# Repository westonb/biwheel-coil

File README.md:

# biwheel-coil
A portable (bike mounted) QCW Tesla Coil.

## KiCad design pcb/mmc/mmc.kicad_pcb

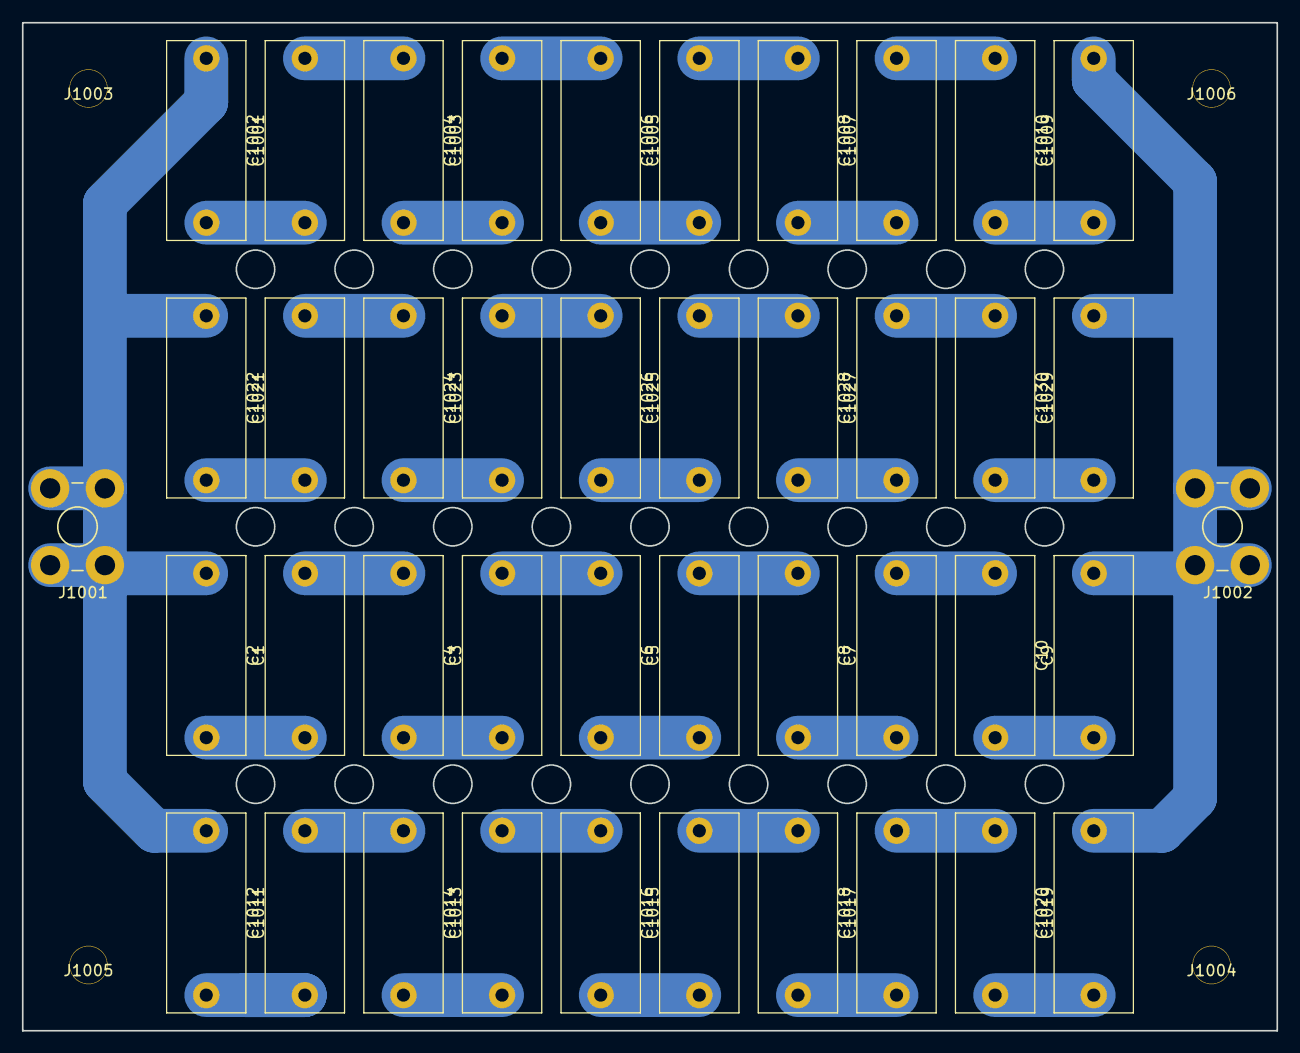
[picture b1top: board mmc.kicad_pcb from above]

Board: 2 copper layers, 114.5 x 92.0 mm, 46 parts (0 on the bottom side), 38 nets.

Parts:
C1, C2, C3, C4, C5, C6, C7, C8, C9, C10, C1001, C1002, C1003, C1004, C1005, C1006, C1007, C1008, C1009, C1010, C1011, C1012, C1013, C1014, C1015, C1016, C1017, C1018, C1019, C1020, C1021, C1022, C1023, C1024, C1025, C1026, C1027, C1028, C1029, C1030: 33n; C_Rect_L18.0mm_W7.0mm_P15.00mm_FKS3_FKP3
J1001, J1002: Conn_01x01_Female; 7693-term
J1003, J1004, J1005, J1006: mounting-hole-nc; M3-mounting-hole-insulated

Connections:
unnamed: C1.1, C1001.1, C1011.1, C1021.1, J1001.1
unnamed: C1.2, C2.1
unnamed: C2.2, C3.1
unnamed: C3.2, C4.1
unnamed: C4.2, C5.1
unnamed: C5.2, C6.1
unnamed: C6.2, C7.1
unnamed: C7.2, C8.1
unnamed: C8.2, C9.1
unnamed: C9.2, C10.1
unnamed: C10.2, C1010.2, C1020.2, C1030.2, J1002.1
unnamed: C1001.2, C1002.1
unnamed: C1002.2, C1003.1
unnamed: C1003.2, C1004.1
unnamed: C1004.2, C1005.1
unnamed: C1005.2, C1006.1
unnamed: C1006.2, C1007.1
unnamed: C1007.2, C1008.1
unnamed: C1008.2, C1009.1
unnamed: C1009.2, C1010.1
unnamed: C1011.2, C1012.1
unnamed: C1012.2, C1013.1
unnamed: C1013.2, C1014.1
unnamed: C1014.2, C1015.1
unnamed: C1015.2, C1016.1
unnamed: C1016.2, C1017.1
unnamed: C1017.2, C1018.1
unnamed: C1018.2, C1019.1
unnamed: C1019.2, C1020.1
unnamed: C1021.2, C1022.1
unnamed: C1022.2, C1023.1
unnamed: C1023.2, C1024.1
unnamed: C1024.2, C1025.1
unnamed: C1025.2, C1026.1
unnamed: C1026.2, C1027.1
unnamed: C1027.2, C1028.1
unnamed: C1028.2, C1029.1
unnamed: C1029.2, C1030.1

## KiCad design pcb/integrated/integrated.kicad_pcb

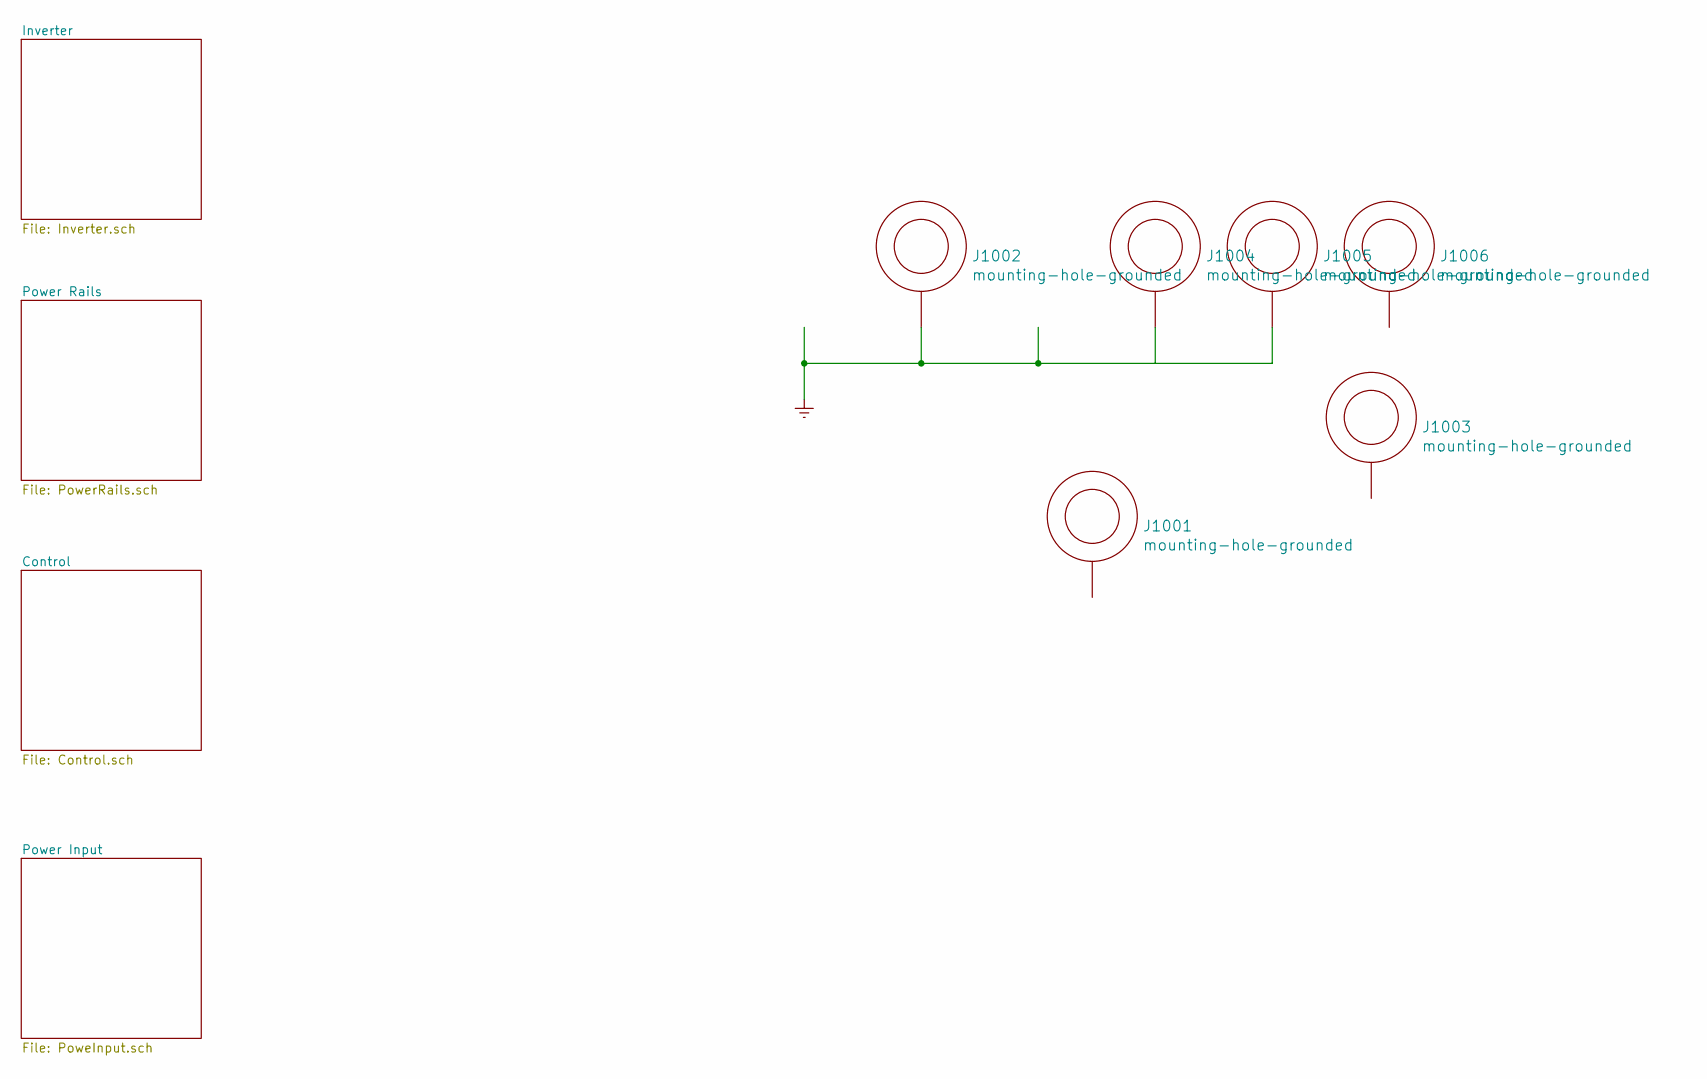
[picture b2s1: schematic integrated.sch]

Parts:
J1001, J1002, J1003, J1004, J1005, J1006: mounting-hole-grounded; M3-tight-fit-pan-head

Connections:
Earth: J1002.1, J1004.1, J1005.1; also elsewhere on the board

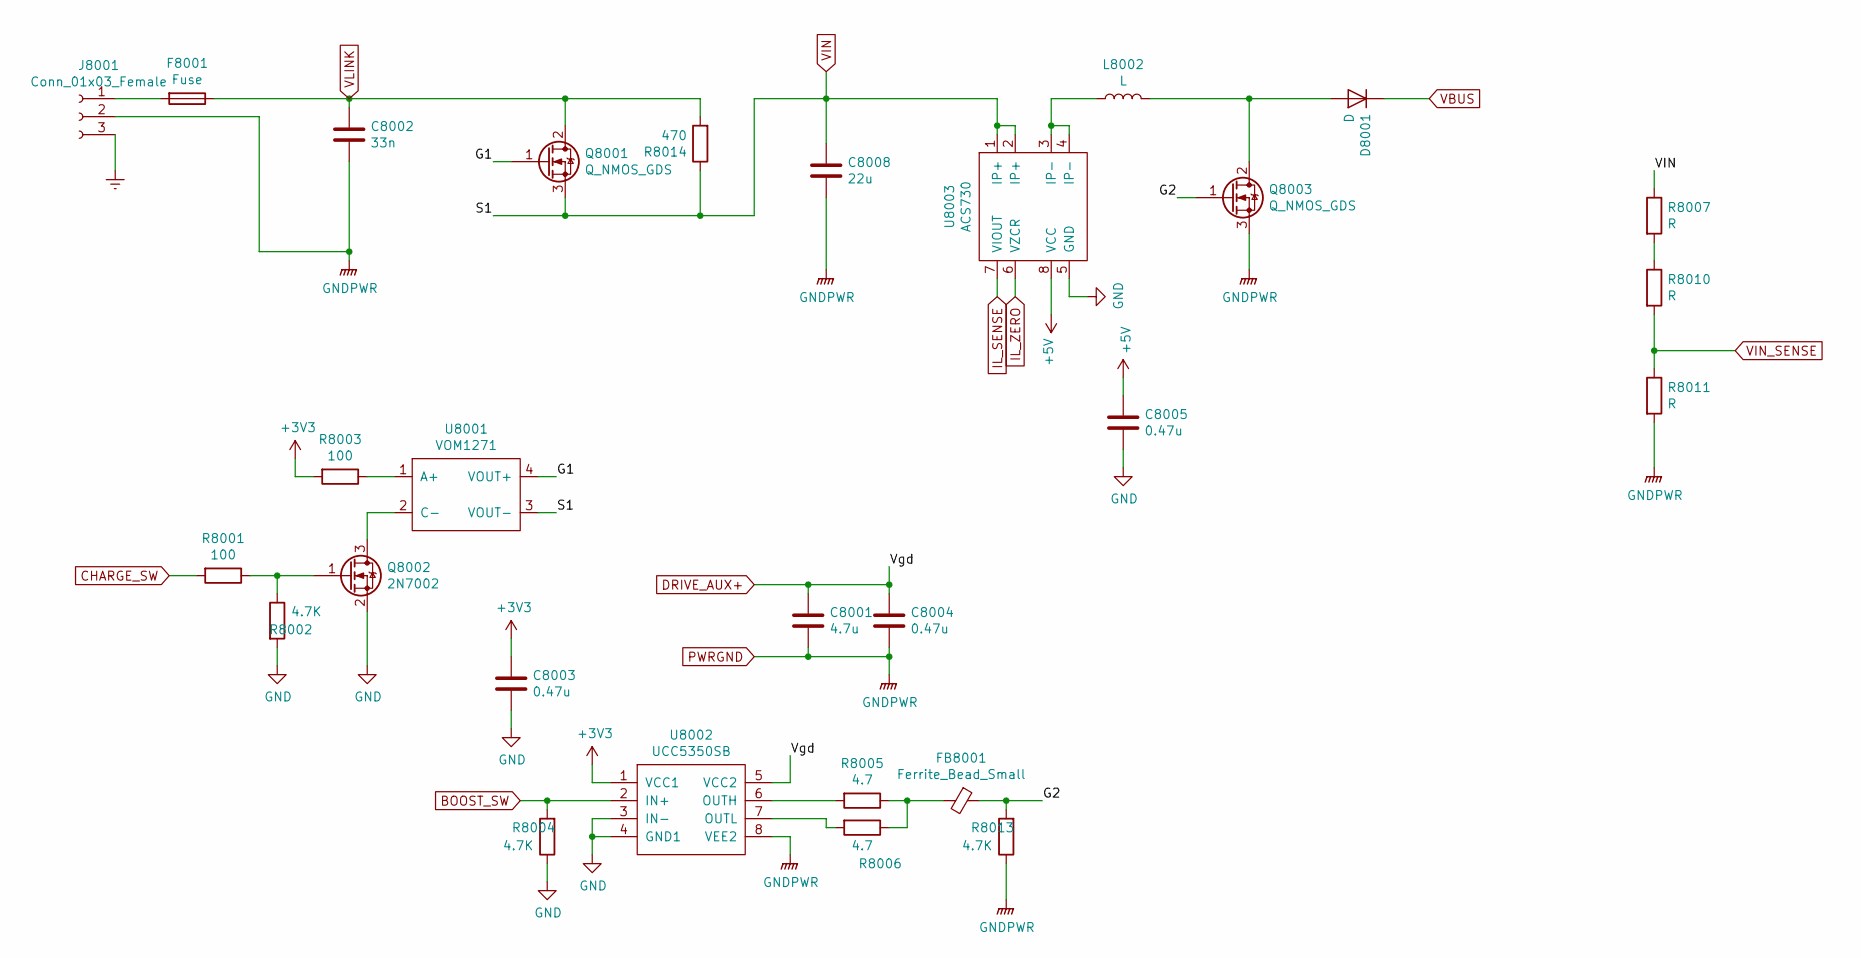
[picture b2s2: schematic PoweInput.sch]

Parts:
C8001: 4.7u; C_0805_2012Metric
C8002: 33n; C_Rect_L18.0mm_W7.0mm_P15.00mm_FKS3_FKP3
C8003, C8004, C8005: 0.47u; C_0603_1608Metric
C8008: 22u; C_Rect_L33.0mm_W13.0mm_P27.50mm_MKS4
D8001: D; TO-247_2_horizontal_under
F8001: Fuse; Fuseholder_Cylinder-5x20mm_Schurter_0031_8201_Horizontal_Op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
FB8001: Ferrite_Bead_Small; L_0805_2012Metric
J8001: Conn_01x03_Female; Terminal-block-plug_3x1_5mm-pitch
L8002: L; T157-Vertical
Q8001, Q8003: Q_NMOS_GDS; TO-247_3_horizontal_under
Q8002: 2N7002; SOT-23
R8001, R8003: 100; R_0402_1005Metric
R8002: 4.7K; R_0402_1005Metric
R8004, R8013: 4.7K; R_0603_1608Metric
R8005, R8006: 4.7; R_0805_2012Metric
R8007, R8010, R8011: R; R_0805_2012Metric
R8014: 470; TO-247_2_horizontal_under
U8001: VOM1271; SO-4_4.4x4.3mm_P2.54mm
U8002: UCC5350SB; SOIC-8_3.9x4.9mm_P1.27mm
U8003: ACS730; SOIC-8_3.9x4.9mm_P1.27mm

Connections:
+3V3: C8003.1, R8003.2, U8002.1 (VCC1); also elsewhere on the board
+5V: C8005.1, U8003.8 (VCC); also elsewhere on the board
/Power Input/G1: Q8001.1 (G), U8001.4 (VOUT+)
/Power Input/G2: FB8001.1, Q8003.1 (G), R8013.2
BOOST_SW: R8004.2, U8002.2 (IN+); also elsewhere on the board
CHARGE_SW: R8001.2; also elsewhere on the board
DRIVE_AUX+: C8001.1, C8004.1, U8002.5 (VCC2); also elsewhere on the board
Earth: J8001.3; also elsewhere on the board
GND: C8003.2, C8005.2, Q8002.2 (S), R8002.2, R8004.1, U8002.3 (IN-), U8002.4 (GND1), U8003.5 (GND); also elsewhere on the board
IL_SENSE: U8003.7 (VIOUT); also elsewhere on the board
IL_ZERO: U8003.6 (VZCR)
unnamed: D8001.2 (A), L8002.2, Q8003.2 (D)
unnamed: F8001.2, J8001.1
unnamed: FB8001.2, R8005.1, R8006.1
unnamed: L8002.1, U8003.3 (IP-), U8003.4 (IP-)
unnamed: Q8002.1 (G), R8001.1, R8002.1
unnamed: Q8002.3 (D), U8001.2 (C-)
unnamed: R8003.1, U8001.1 (A+)
unnamed: R8005.2, U8002.6 (OUTH)
unnamed: R8006.2, U8002.7 (OUTL)
unnamed: R8007.2, R8010.1
PWRGND: C8001.2, C8002.2, C8004.2, C8008.2, J8001.2, Q8003.3 (S), R8011.2, R8013.1, U8002.8 (VEE2); also elsewhere on the board
VBUS: D8001.1 (K); also elsewhere on the board
VIN: C8008.1, Q8001.3 (S), R8007.1, R8014.1, U8001.3 (VOUT-), U8003.1 (IP+), U8003.2 (IP+)
VIN_SENSE: R8010.2, R8011.1; also elsewhere on the board
VLINK: C8002.1, F8001.1, Q8001.2 (D), R8014.2; also elsewhere on the board

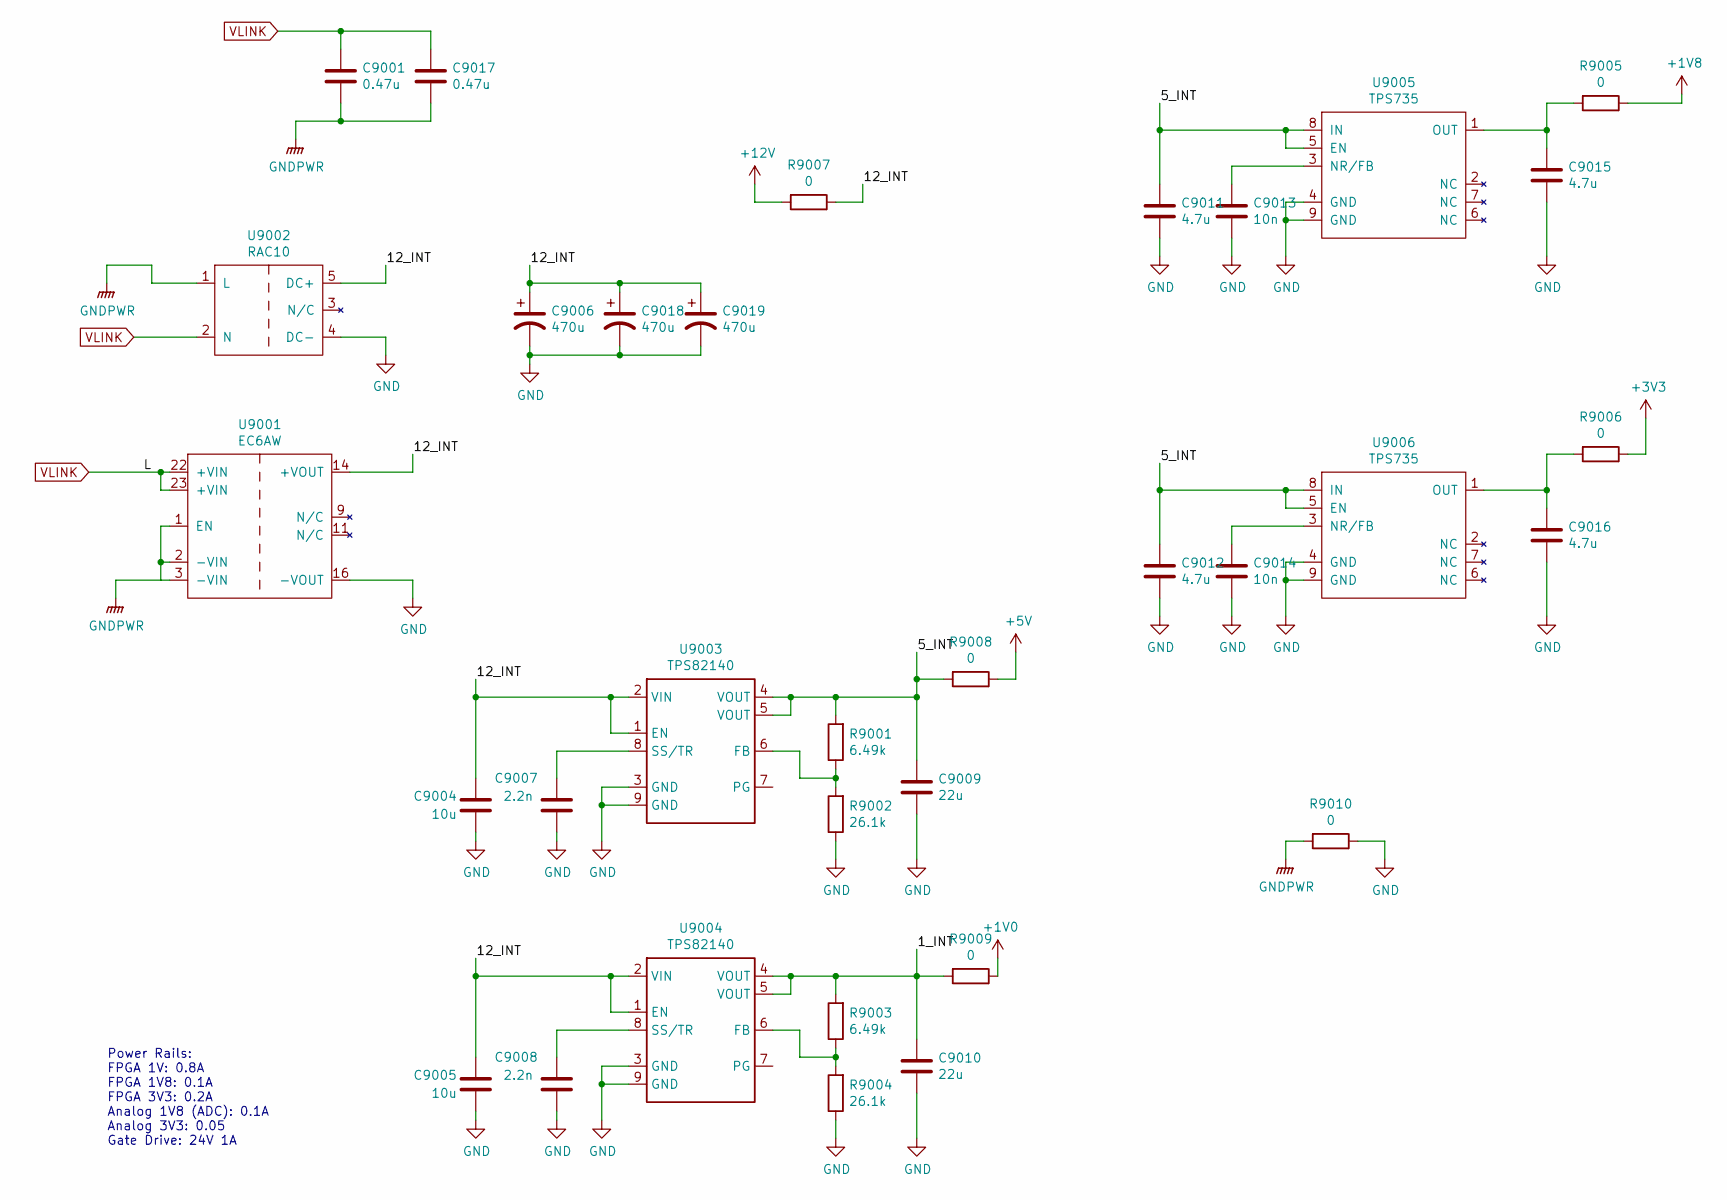
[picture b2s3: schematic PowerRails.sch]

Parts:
C9001, C9017: 0.47u; C_1812_4532Metric
C9004, C9005: 10u; C_1206_3216Metric
C9006, C9018, C9019: 470u; CP_Radial_D10.0mm_P5.00mm
C9007, C9008: 2.2n; C_0402_1005Metric
C9009, C9010: 22u; C_0805_2012Metric
C9011, C9012, C9015, C9016: 4.7u; C_0603_1608Metric
C9013, C9014: 10n; C_0402_1005Metric
R9001, R9003: 6.49k; R_0402_1005Metric
R9002, R9004: 26.1k; R_0402_1005Metric
R9005, R9006, R9007, R9008, R9009, R9010: 0; R_0805_2012Metric
U9001: EC6AW
U9002: RAC10
U9003, U9004: TPS82140; uSil-8
U9005, U9006: TPS735; SON-8_EP

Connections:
+1V0: R9009.1; also elsewhere on the board
+1V8: R9005.1; also elsewhere on the board
+3V3: R9006.1; also elsewhere on the board
+5V: R9008.1; also elsewhere on the board
+12V: R9007.2; also elsewhere on the board
/Power Rails/1_INT: C9010.1, R9003.2, R9009.2, U9004.4 (VOUT), U9004.5 (VOUT)
/Power Rails/5_INT: C9009.1, C9011.2, C9012.2, R9001.2, R9008.2, U9003.4 (VOUT), U9003.5 (VOUT), U9005.5 (EN), U9005.8 (IN), U9006.5 (EN), U9006.8 (IN)
/Power Rails/12_INT: C9004.1, C9005.1, C9006.1, C9018.1, C9019.1, R9007.1, U9001.14 (+VOUT), U9002.5 (DC+), U9003.1 (EN), U9003.2 (VIN), U9004.1 (EN), U9004.2 (VIN)
GND: C9004.2, C9005.2, C9006.2, C9007.2, C9008.2, C9009.2, C9010.2, C9011.1, C9012.1, C9013.1, C9014.1, C9015.1, C9016.1, C9018.2, C9019.2, R9002.1, R9004.1, R9010.1, U9001.16 (-VOUT), U9002.4 (DC-), U9003.3 (GND), U9003.9 (GND), U9004.3 (GND), U9004.9 (GND), U9005.4 (GND), U9005.9 (GND), U9006.4 (GND), U9006.9 (GND); also elsewhere on the board
unnamed: C9007.1, U9003.8 (SS/TR)
unnamed: C9008.1, U9004.8 (SS/TR)
unnamed: C9013.2, U9005.3 (NR/FB)
unnamed: C9014.2, U9006.3 (NR/FB)
unnamed: C9015.2, R9005.2, U9005.1 (OUT)
unnamed: C9016.2, R9006.2, U9006.1 (OUT)
unnamed: R9001.1, R9002.2, U9003.6 (FB)
unnamed: R9003.1, R9004.2, U9004.6 (FB)
PWRGND: C9001.2, C9017.2, R9010.2, U9001.1 (EN), U9001.2 (-VIN), U9001.3 (-VIN), U9002.1 (L); also elsewhere on the board
VLINK: C9001.1, C9017.1, U9001.22 (+VIN), U9001.23 (+VIN), U9002.2 (N); also elsewhere on the board

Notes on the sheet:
Power Rails: FPGA 1V: 0.8A FPGA 1V8: 0.1A FPGA 3V3: 0.2A Analog 1V8 (ADC): 0.1A Analog 3V3: 0.05 Gate Drive: 24V 1A

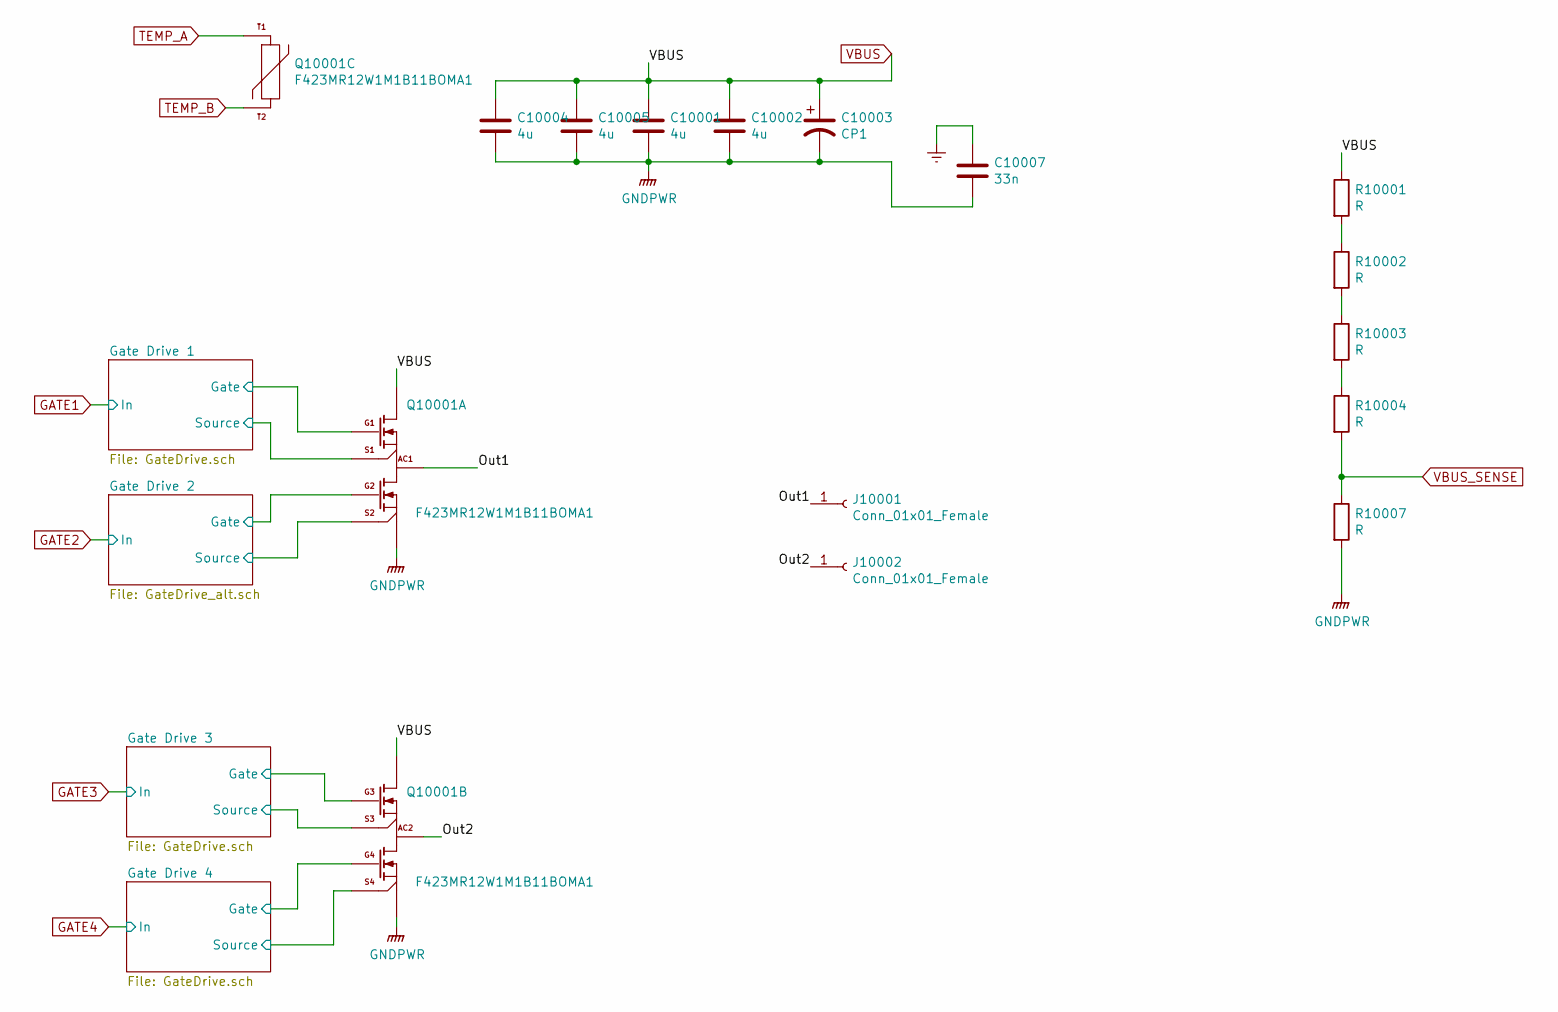
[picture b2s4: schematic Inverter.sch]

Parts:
C10001, C10002, C10004, C10005: 4u; C_Rect_L31.5mm_W13.0mm_P27.50mm_MKS4
C10003: CP1; CAP_77mm_stud_horizontal
C10007: 33n; C_Rect_L18.0mm_W7.0mm_P15.00mm_FKS3_FKP3
J10001, J10002: Conn_01x01_Female; 7693-term
Q10001: F423MR12W1M1B11BOMA1
R10001, R10002, R10003, R10004, R10007: R; R_0805_2012Metric

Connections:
/Inverter/Gate Drive 1/Gate: Q10001.G1; also elsewhere on the board
/Inverter/Gate Drive 2/Gate: Q10001.G2; also elsewhere on the board
/Inverter/Gate Drive 3/Gate: Q10001.G3; also elsewhere on the board
/Inverter/Gate Drive 3/Source: Q10001.S3; also elsewhere on the board
/Inverter/Gate Drive 4/Gate: Q10001.G4; also elsewhere on the board
/Inverter/Gate Drive 4/Source: Q10001.S4; also elsewhere on the board
/Inverter/Out1: J10001.1, Q10001.AC1
/Inverter/Out2: J10002.1, Q10001.AC2
Earth: C10007.1; also elsewhere on the board
unnamed: R10001.2, R10002.1
unnamed: R10002.2, R10003.1
unnamed: R10003.2, R10004.1
PWRGND: C10001.2, C10002.2, C10003.2, C10004.2, C10005.2, C10007.2, Q10001.DC-, R10007.2; also elsewhere on the board
TEMP_A: Q10001.T1; also elsewhere on the board
TEMP_B: Q10001.T2; also elsewhere on the board
VBUS: C10001.1, C10002.1, C10003.1, C10004.1, C10005.1, Q10001.DC+, R10001.1; also elsewhere on the board
VBUS_SENSE: R10004.2, R10007.1; also elsewhere on the board

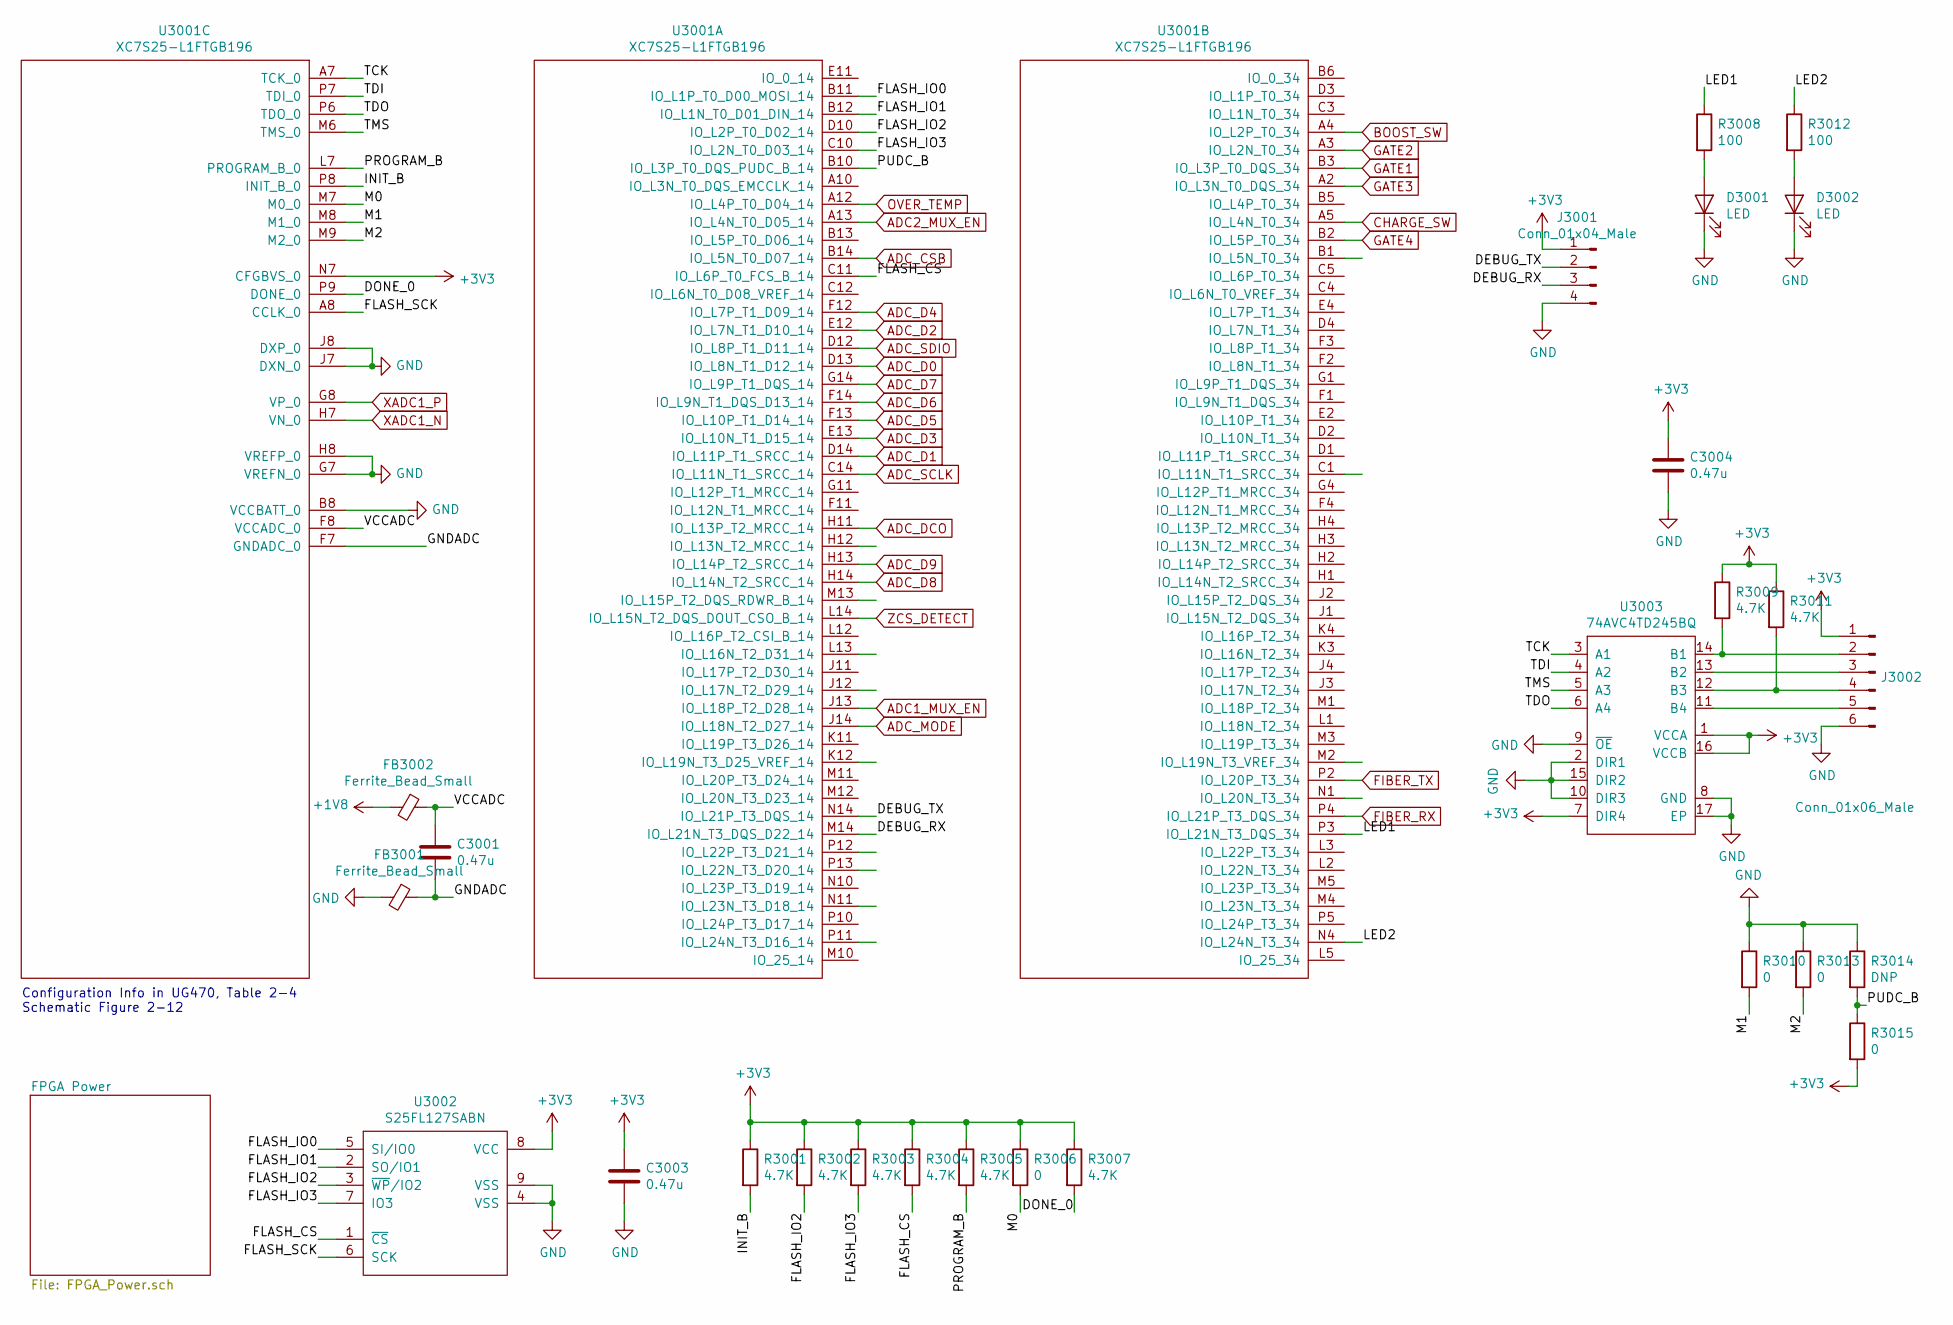
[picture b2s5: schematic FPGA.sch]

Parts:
C3001, C3003, C3004: 0.47u; C_0402_1005Metric
D3001, D3002: LED; LED_0805_2012Metric
FB3001, FB3002: Ferrite_Bead_Small; L_0402_1005Metric
J3001: Conn_01x04_Male; PinHeader_1x04_P2.54mm_Vertical
J3002: Conn_01x06_Male; PinHeader_1x06_P2.54mm_Vertical
R3001, R3002, R3003, R3004, R3005, R3007, R3009, R3011: 4.7K; R_0402_1005Metric
R3006, R3010, R3013, R3015: 0; R_0402_1005Metric
R3008, R3012: 100; R_0402_1005Metric
R3014: DNP; R_0402_1005Metric
U3001: XC7S25-L1FTGB196; FTGB196
U3002: S25FL127SABN; WSON-8-1EP_6x5mm_P1.27mm_EP3.4x4mm
U3003: 74AVC4TD245BQ; DHVQFN16

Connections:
+1V8: FB3002.2; also elsewhere on the board
+3V3: C3003.1, C3004.1, J3001.1, J3002.1, R3001.1, R3002.1, R3003.1, R3004.1, R3005.1, R3006.1, R3007.1, R3009.1, R3011.1, R3015.2, U3001.N7 (CFGBVS_0), U3002.8 (VCC), U3003.1 (VCCA), U3003.7 (DIR4), U3003.16 (VCCB); also elsewhere on the board
/Control/FPGA/DEBUG_RX: J3001.3, U3001.M14 (IO_L21N_T3_DQS_D22_14)
/Control/FPGA/DEBUG_TX: J3001.2, U3001.N14 (IO_L21P_T3_DQS_14)
/Control/FPGA/DONE_0: R3007.2, U3001.P9 (DONE_0)
/Control/FPGA/FLASH_CS: R3004.2, U3001.C11 (IO_L6P_T0_FCS_B_14), U3002.1 (~CS)
/Control/FPGA/FLASH_IO0: U3001.B11 (IO_L1P_T0_D00_MOSI_14), U3002.5 (SI/IO0)
/Control/FPGA/FLASH_IO1: U3001.B12 (IO_L1N_T0_D01_DIN_14), U3002.2 (SO/IO1)
/Control/FPGA/FLASH_IO2: R3002.2, U3001.D10 (IO_L2P_T0_D02_14), U3002.3 (~WP~/IO2)
/Control/FPGA/FLASH_IO3: R3003.2, U3001.C10 (IO_L2N_T0_D03_14), U3002.7 (IO3)
/Control/FPGA/FLASH_SCK: U3001.A8 (CCLK_0), U3002.6 (SCK)
/Control/FPGA/GNDADC: C3001.2, FB3001.1, U3001.F7 (GNDADC_0)
/Control/FPGA/INIT_B: R3001.2, U3001.P8 (INIT_B_0)
/Control/FPGA/LED1: R3008.1, U3001.P3 (IO_L21N_T3_DQS_34)
/Control/FPGA/LED2: R3012.1, U3001.N4 (IO_L24N_T3_34)
/Control/FPGA/M0: R3006.2, U3001.M7 (M0_0)
/Control/FPGA/M1: R3010.2, U3001.M8 (M1_0)
/Control/FPGA/M2: R3013.2, U3001.M9 (M2_0)
/Control/FPGA/PROGRAM_B: R3005.2, U3001.L7 (PROGRAM_B_0)
/Control/FPGA/PUDC_B: R3014.2, R3015.1, U3001.B10 (IO_L3P_T0_DQS_PUDC_B_14)
/Control/FPGA/TCK: U3001.A7 (TCK_0), U3003.3 (A1)
/Control/FPGA/TDI: U3001.P7 (TDI_0), U3003.4 (A2)
/Control/FPGA/TDO: U3001.P6 (TDO_0), U3003.6 (A4)
/Control/FPGA/TMS: U3001.M6 (TMS_0), U3003.5 (A3)
/Control/FPGA/VCCADC: C3001.1, FB3002.1, U3001.F8 (VCCADC_0)
ADC1_MUX_EN: U3001.J13 (IO_L18P_T2_D28_14); also elsewhere on the board
ADC2_MUX_EN: U3001.A13 (IO_L4N_T0_D05_14); also elsewhere on the board
ADC_CSB: U3001.B14 (IO_L5N_T0_D07_14); also elsewhere on the board
ADC_D0: U3001.D13 (IO_L8N_T1_D12_14); also elsewhere on the board
ADC_D1: U3001.D14 (IO_L11P_T1_SRCC_14); also elsewhere on the board
ADC_D2: U3001.E12 (IO_L7N_T1_D10_14); also elsewhere on the board
ADC_D3: U3001.E13 (IO_L10N_T1_D15_14); also elsewhere on the board
ADC_D4: U3001.F12 (IO_L7P_T1_D09_14); also elsewhere on the board
ADC_D5: U3001.F13 (IO_L10P_T1_D14_14); also elsewhere on the board
ADC_D6: U3001.F14 (IO_L9N_T1_DQS_D13_14); also elsewhere on the board
ADC_D7: U3001.G14 (IO_L9P_T1_DQS_14); also elsewhere on the board
ADC_D8: U3001.H14 (IO_L14N_T2_SRCC_14); also elsewhere on the board
ADC_D9: U3001.H13 (IO_L14P_T2_SRCC_14); also elsewhere on the board
ADC_DCO: U3001.H11 (IO_L13P_T2_MRCC_14); also elsewhere on the board
ADC_MODE: U3001.J14 (IO_L18N_T2_D27_14); also elsewhere on the board
ADC_SCLK: U3001.C14 (IO_L11N_T1_SRCC_14); also elsewhere on the board
ADC_SDIO: U3001.D12 (IO_L8P_T1_D11_14); also elsewhere on the board
BOOST_SW: U3001.A4 (IO_L2P_T0_34); also elsewhere on the board
CHARGE_SW: U3001.A5 (IO_L4N_T0_34); also elsewhere on the board
FIBER_RX: U3001.P4 (IO_L21P_T3_DQS_34); also elsewhere on the board
FIBER_TX: U3001.P2 (IO_L20P_T3_34); also elsewhere on the board
GATE1: U3001.B3 (IO_L3P_T0_DQS_34); also elsewhere on the board
GATE2: U3001.A3 (IO_L2N_T0_34); also elsewhere on the board
GATE3: U3001.A2 (IO_L3N_T0_DQS_34); also elsewhere on the board
GATE4: U3001.B2 (IO_L5P_T0_34); also elsewhere on the board
GND: C3003.2, C3004.2, D3001.1 (K), D3002.1 (K), FB3001.2, J3001.4, J3002.6, R3010.1, R3013.1, R3014.1, U3001.B8 (VCCBATT_0), U3001.G7 (VREFN_0), U3001.H8 (VREFP_0), U3001.J7 (DXN_0), U3001.J8 (DXP_0), U3002.4 (VSS), U3002.9 (VSS), U3003.2 (DIR1), U3003.8 (GND), U3003.9 (~OE), U3003.10 (DIR3), U3003.15 (DIR2), U3003.17 (EP); also elsewhere on the board
unnamed: D3001.2 (A), R3008.2
unnamed: D3002.2 (A), R3012.2
unnamed: J3002.2, R3009.2, U3003.14 (B1)
unnamed: J3002.3, U3003.13 (B2)
unnamed: J3002.4, R3011.2, U3003.12 (B3)
unnamed: J3002.5, U3003.11 (B4)
OVER_TEMP: U3001.A12 (IO_L4P_T0_D04_14); also elsewhere on the board
XADC1_N: U3001.H7 (VN_0); also elsewhere on the board
XADC1_P: U3001.G8 (VP_0); also elsewhere on the board
ZCS_DETECT: U3001.L14 (IO_L15N_T2_DQS_DOUT_CSO_B_14); also elsewhere on the board

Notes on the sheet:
Configuration Info in UG470, Table 2-4 Schematic Figure 2-12

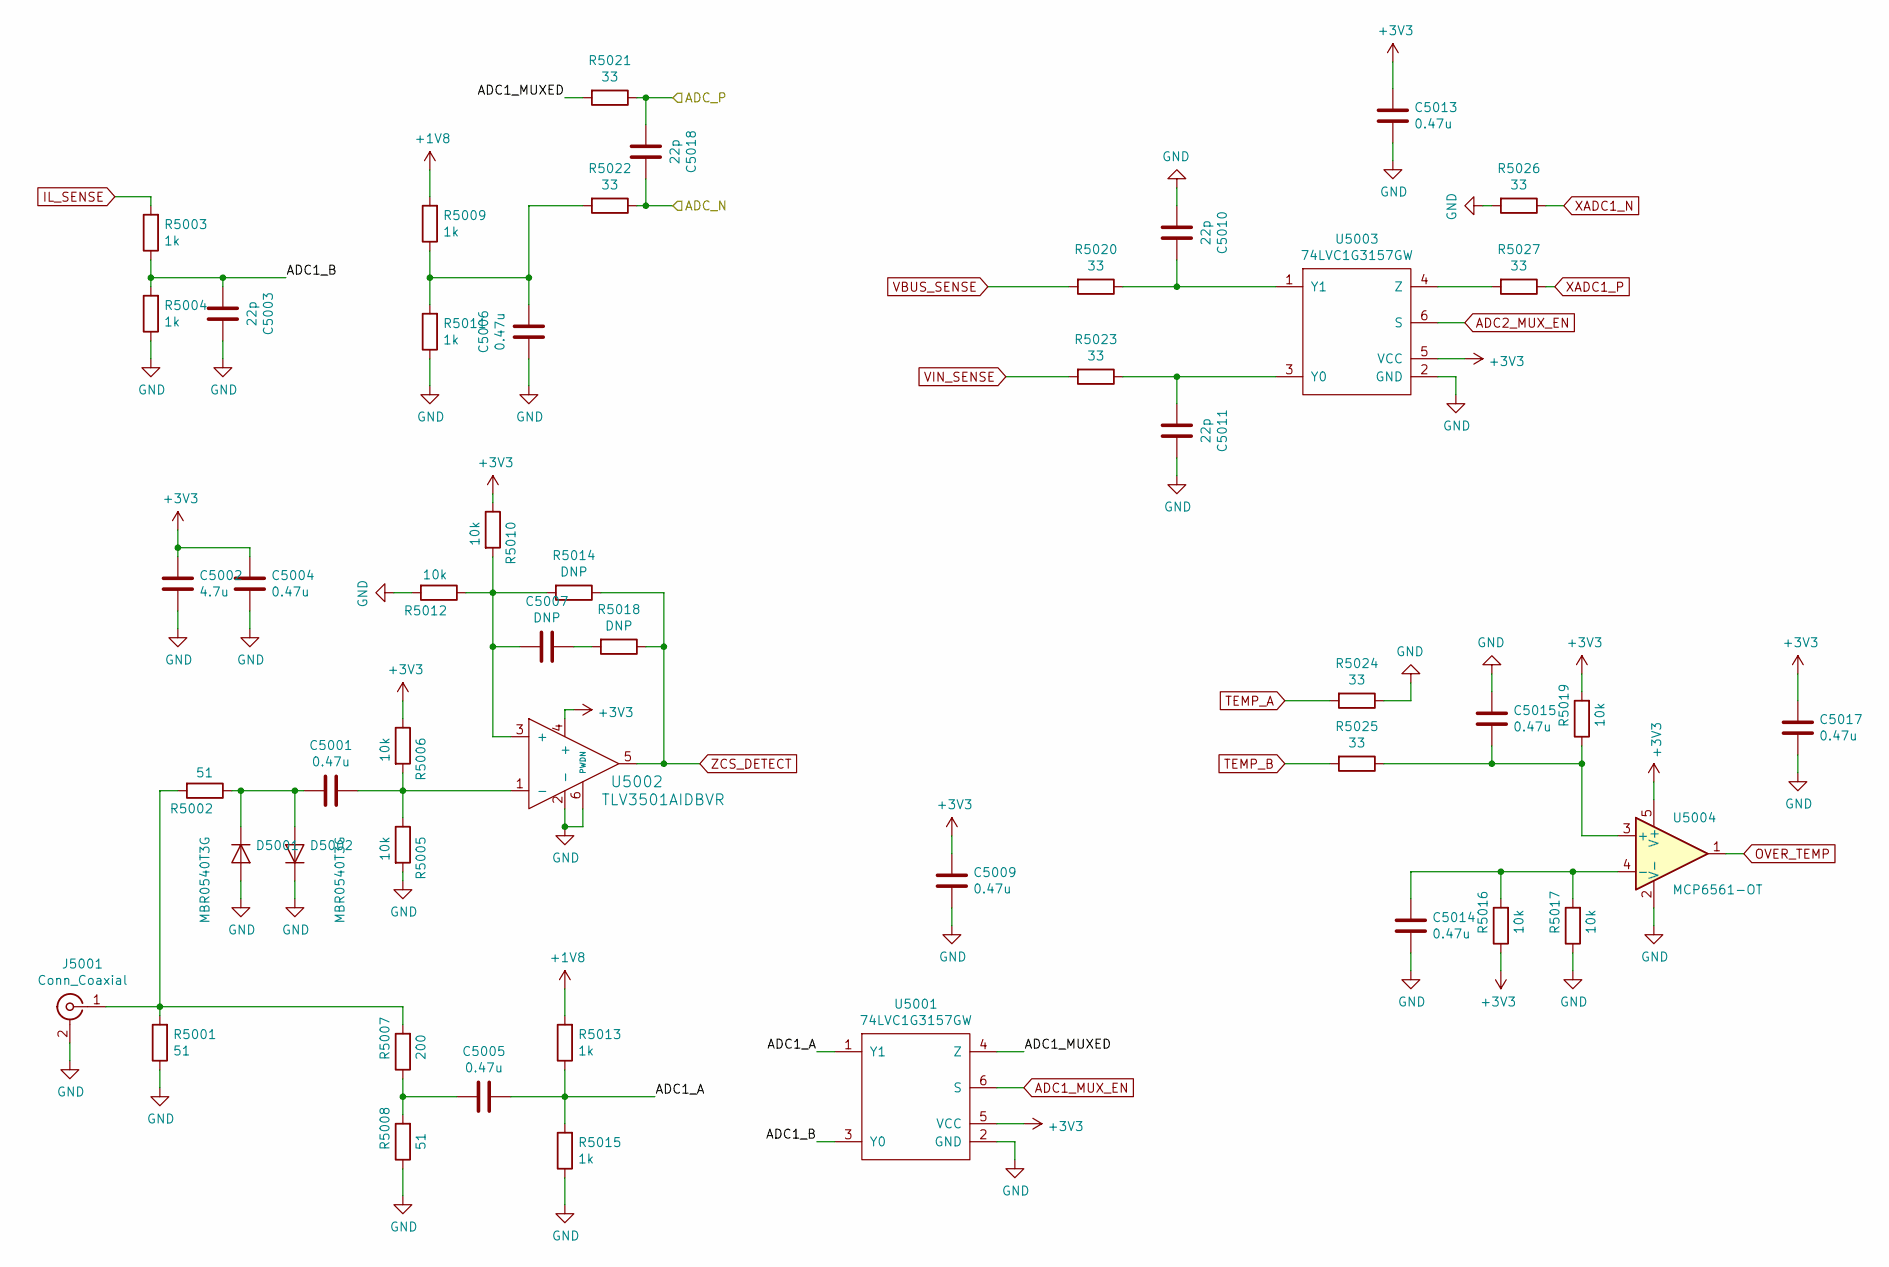
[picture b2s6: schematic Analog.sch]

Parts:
C5001, C5004, C5005, C5006, C5009, C5013, C5014, C5015, C5017: 0.47u; C_0402_1005Metric
C5002: 4.7u; C_0402_1005Metric
C5003, C5010, C5011, C5018: 22p; C_0402_1005Metric
C5007: DNP; C_0402_1005Metric
D5001, D5002: MBR0540T3G; D_SOD-123
J5001: Conn_Coaxial; SMA_Amphenol_132134-16_Vertical
R5001: 51; R_2512_6332Metric
R5002, R5008: 51; R_1206_3216Metric
R5003, R5004, R5009, R5011, R5013, R5015: 1k; R_0402_1005Metric
R5005, R5006, R5010, R5012, R5016, R5017, R5019: 10k; R_0402_1005Metric
R5007: 200; R_1206_3216Metric
R5014, R5018: DNP; R_0402_1005Metric
R5020, R5021, R5022, R5023, R5024, R5025, R5026, R5027: 33; R_0402_1005Metric
U5001, U5003: 74LVC1G3157GW; SOT-363_SC-70-6
U5002: TLV3501AIDBVR; SOT-23-6
U5004: MCP6561-OT; SOT-23-5

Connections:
+1V8: R5009.2, R5013.2; also elsewhere on the board
+3V3: C5002.2, C5004.2, C5009.2, C5013.2, C5017.2, R5006.1, R5010.1, R5016.1, R5019.2, U5001.5 (VCC), U5002.4 (+), U5003.5 (VCC), U5004.5 (V+); also elsewhere on the board
/Control/ADC/ADC_N: C5018.1, R5022.1; also elsewhere on the board
/Control/ADC/ADC_P: C5018.2, R5021.1; also elsewhere on the board
/Control/Analog/ADC1_A: C5005.1, R5013.1, R5015.2, U5001.1 (Y1)
/Control/Analog/ADC1_B: C5003.2, R5003.1, R5004.2, U5001.3 (Y0)
/Control/Analog/ADC1_MUXED: R5021.2, U5001.4 (Z)
ADC1_MUX_EN: U5001.6 (S); also elsewhere on the board
ADC2_MUX_EN: U5003.6 (S); also elsewhere on the board
GND: C5002.1, C5003.1, C5004.1, C5006.2, C5009.1, C5010.2, C5011.1, C5013.1, C5014.1, C5015.2, C5017.1, D5001.2 (A), D5002.1 (K), J5001.2 (Ext), R5001.1, R5004.1, R5005.2, R5008.1, R5011.1, R5012.2, R5015.1, R5017.1, R5024.1, R5026.2, U5001.2 (GND), U5002.2 (-), U5002.6 (PWDN), U5003.2 (GND), U5004.2 (V-); also elsewhere on the board
IL_SENSE: R5003.2; also elsewhere on the board
unnamed: C5001.1, R5005.1, R5006.2, U5002.1 (-)
unnamed: C5001.2, D5001.1 (K), D5002.2 (A), R5002.1
unnamed: C5005.2, R5007.1, R5008.2
unnamed: C5006.1, R5009.1, R5011.2, R5022.2
unnamed: C5007.1, R5018.2
unnamed: C5007.2, R5010.2, R5012.1, R5014.2, U5002.3 (+)
unnamed: C5010.1, R5020.1, U5003.1 (Y1)
unnamed: C5011.2, R5023.1, U5003.3 (Y0)
unnamed: C5014.2, R5016.2, R5017.2, U5004.4 (-)
unnamed: C5015.1, R5019.1, R5025.1, U5004.3 (+)
unnamed: J5001.1 (In), R5001.2, R5002.2, R5007.2
unnamed: R5027.2, U5003.4 (Z)
OVER_TEMP: U5004.1; also elsewhere on the board
TEMP_A: R5024.2; also elsewhere on the board
TEMP_B: R5025.2; also elsewhere on the board
VBUS_SENSE: R5020.2; also elsewhere on the board
VIN_SENSE: R5023.2; also elsewhere on the board
XADC1_N: R5026.1; also elsewhere on the board
XADC1_P: R5027.1; also elsewhere on the board
ZCS_DETECT: R5014.1, R5018.1, U5002.5; also elsewhere on the board
